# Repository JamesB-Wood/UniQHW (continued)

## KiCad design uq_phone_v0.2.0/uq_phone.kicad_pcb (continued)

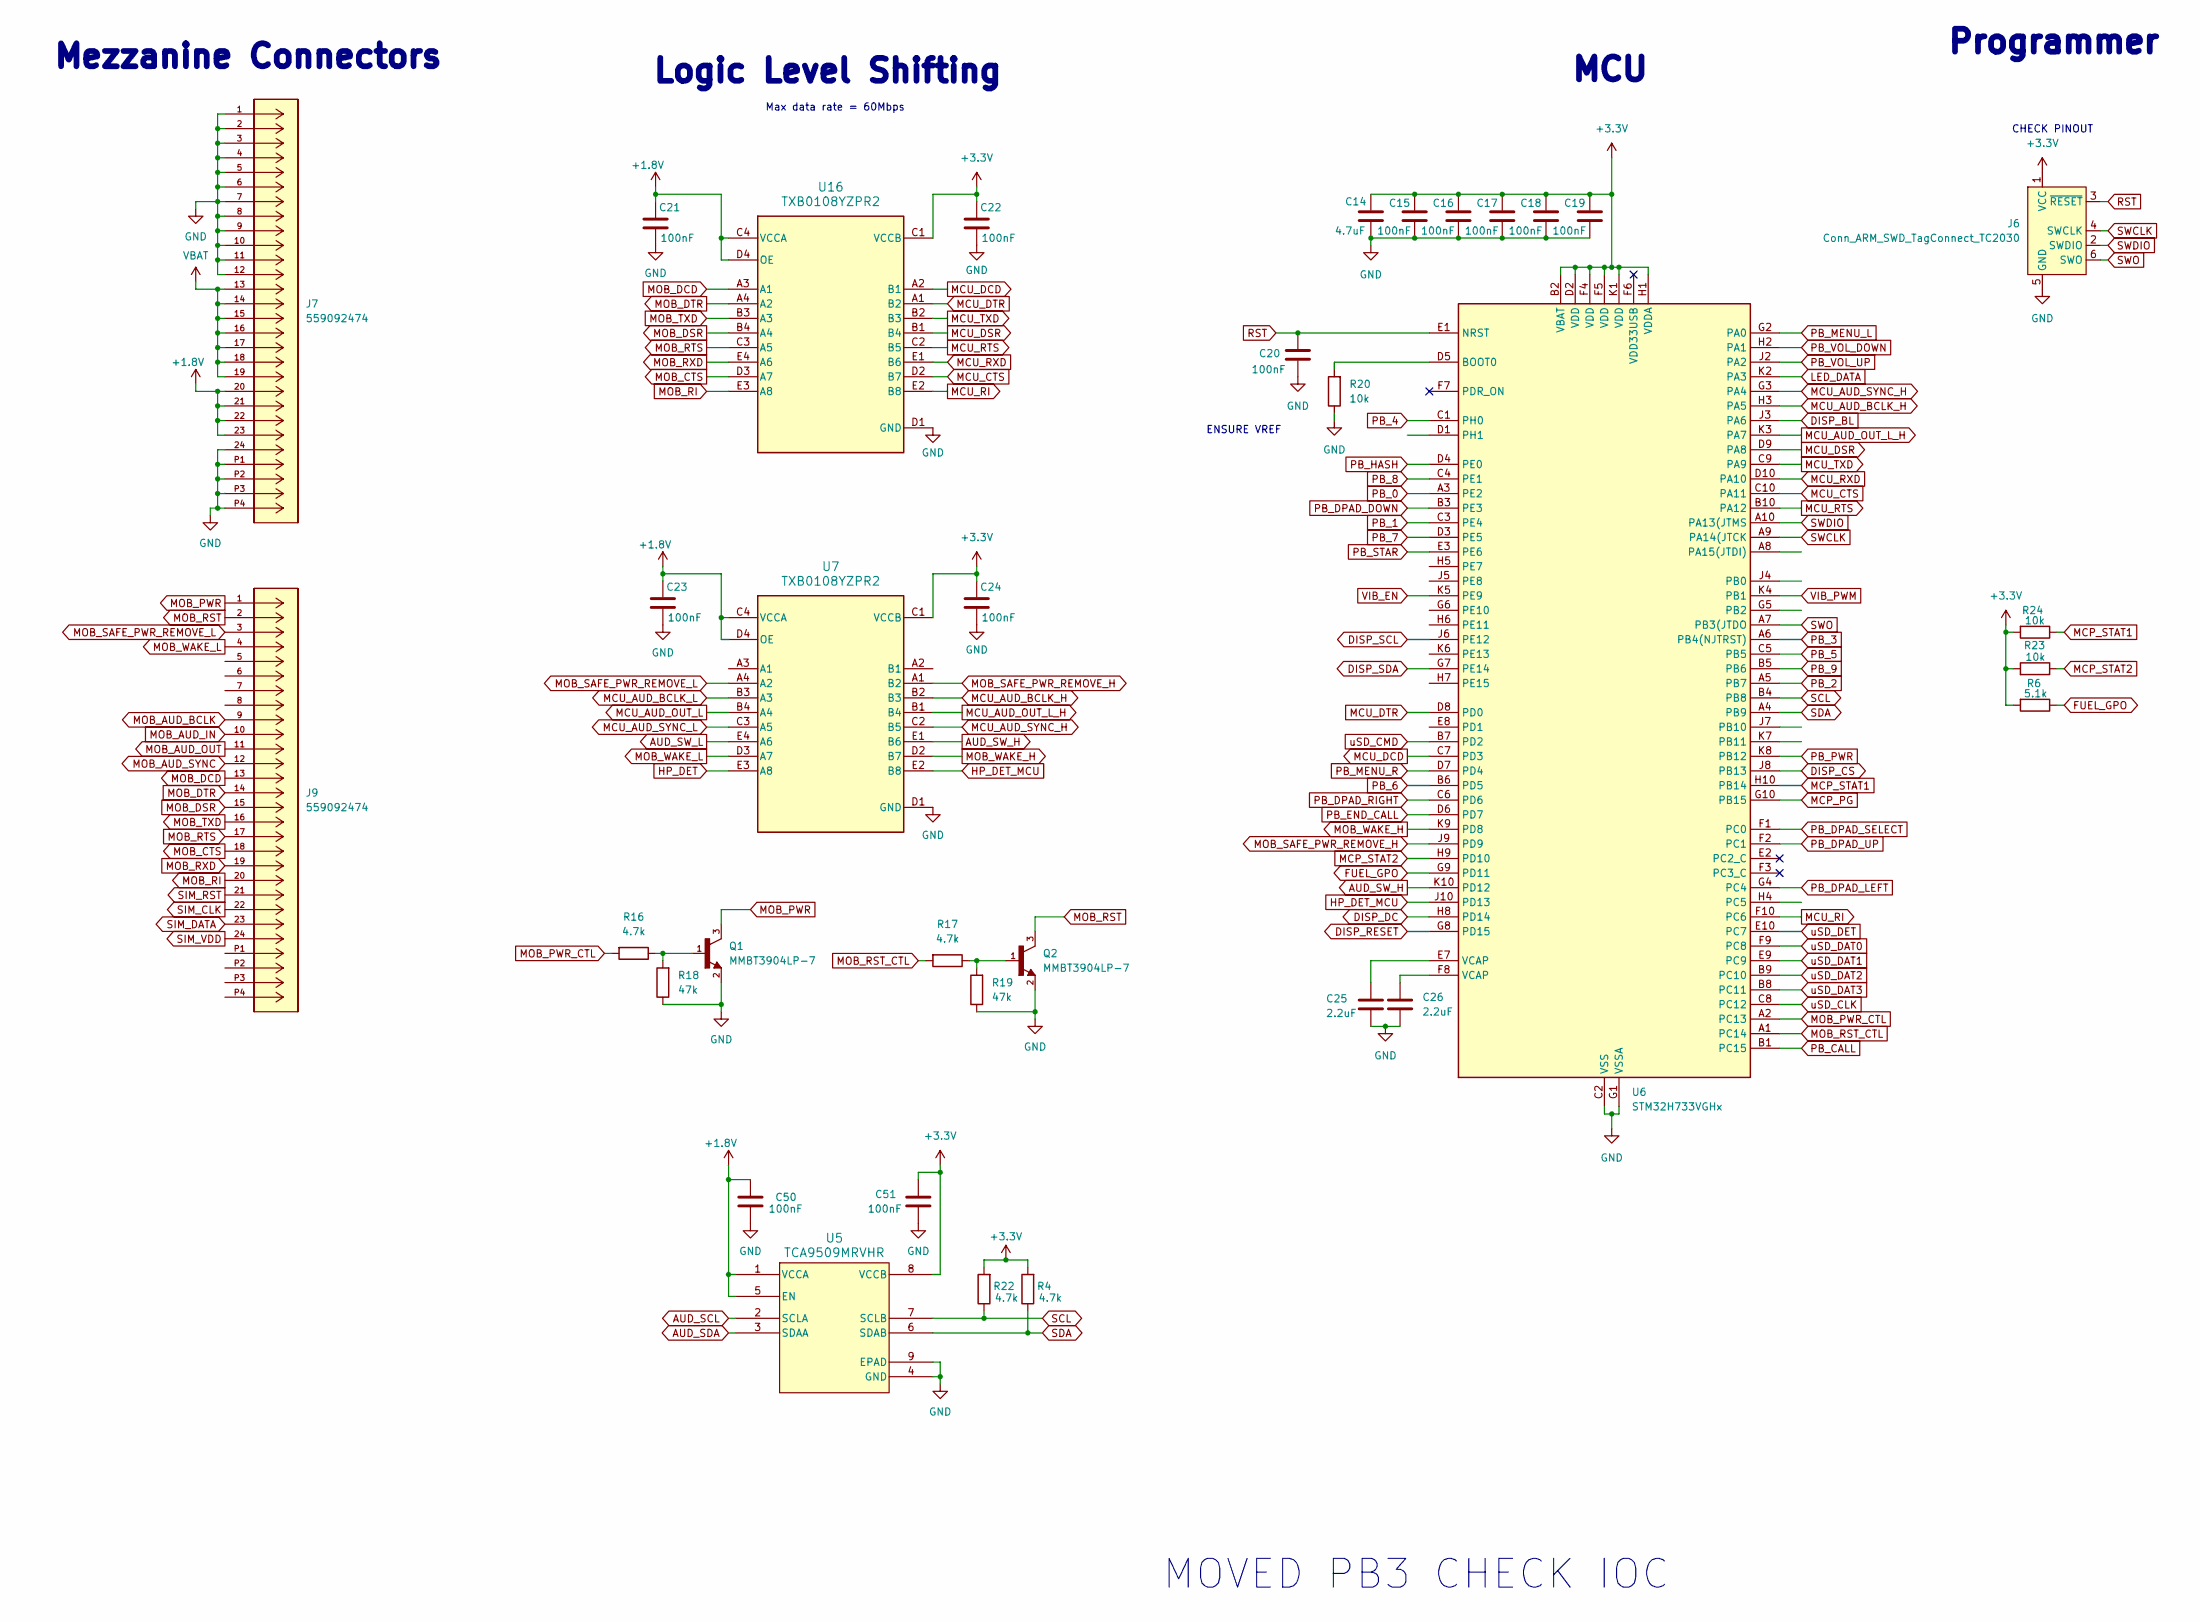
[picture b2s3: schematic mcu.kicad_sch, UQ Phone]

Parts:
C14: 4.7uF; C_0201_0603Metric; LCSC PN C335103
C15, C16, C17, C18, C19, C20, C21, C22, C23, C24, C50, C51: 100nF; C_0201_0603Metric; LCSC PN C160831
C25, C26: 2.2uF; C_0402_1005Metric; LCSC PN C107369
J6: Conn_ARM_SWD_TagConnect_TC2030; Tag-Connect_TC2030-IDC-FP_2x03_P1.27mm_Vertical
J7, J9: 559092474; CON_559092474; MANUFACTURER_PART_NUMBER 559092474; DigiKey_Part_Number WM3787TR-ND
Q1, Q2: MMBT3904LP-7; DFN101X61X53-3N; DigiKey_Part_Number MMBT3904LP-7DITR-ND
R4, R16, R17, R22: 4.7k; R_0201_0603Metric; LCSC PN C138135
R6: 5.1k; R_0201_0603Metric; LCSC PN C274341
R18, R19: 47k; R_0201_0603Metric; LCSC PN C138139
R20, R23, R24: 10k; R_0201_0603Metric; LCSC PN C106225
U5: TCA9509MRVHR; RVH8_0P4X0P4; LCSC PN C2652478
U6: STM32H733VGHx; TFBGA-100_8x8mm_Layout10x10_P0.8mm
U7, U16: TXB0108YZPR2; YZP20

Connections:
+1.8V: C21.1, C23.1, C50.1, J7.20, J7.21, J7.22, J7.23, U5.1 (VCCA), U5.5 (EN), U7.C4 (VCCA), U7.D4 (OE), U16.C4 (VCCA), U16.D4 (OE); also elsewhere on the board
+3.3V: C14.1, C15.2, C16.2, C17.2, C18.2, C19.2, C22.1, C24.1, C51.1, J6.1 (VCC), R4.2, R6.2, R22.2, R23.2, R24.2, U5.8 (VCCB), U6.B2 (VBAT), U6.D2 (VDD), U6.F4 (VDD), U6.F5 (VDD), U6.H1 (VDDA), U6.K1 (VDD), U7.C1 (VCCB), U16.C1 (VCCB); also elsewhere on the board
AUD_SCL: U5.2 (SCLA); also elsewhere on the board
AUD_SDA: U5.3 (SDAA); also elsewhere on the board
AUD_SW_H: U6.K10 (PD12), U7.E1 (B6)
AUD_SW_L: U7.E4 (A6); also elsewhere on the board
DISP_BL: U6.J3 (PA6); also elsewhere on the board
DISP_CS: U6.J8 (PB13); also elsewhere on the board
DISP_DC: U6.H8 (PD14); also elsewhere on the board
DISP_RESET: U6.G8 (PD15); also elsewhere on the board
DISP_SCL: U6.J6 (PE12); also elsewhere on the board
DISP_SDA: U6.G7 (PE14); also elsewhere on the board
FUEL_GPO: R6.1, U6.G9 (PD11); also elsewhere on the board
GND: C14.2, C15.1, C16.1, C17.1, C18.1, C19.1, C20.1, C21.2, C22.2, C23.2, C24.2, C25.2, C26.2, C50.2, C51.2, J6.5 (GND), J7.1, J7.2, J7.3, J7.4, J7.5, J7.6, J7.7, J7.8, J7.9, J7.10, J7.11, J7.12, J7.24, J7.P1, J7.P2, J7.P3, J7.P4, Q1.2, Q2.2, R18.1, R19.1, R20.1, U5.4 (GND), U5.9 (EPAD), U6.C2 (VSS), U6.E4 (VSS), U6.E5 (VSS), U6.E6 (VSS), U6.G1 (VSSA), U6.J1 (VSS), U7.D1 (GND), U16.D1 (GND); also elsewhere on the board
HP_DET: U7.E3 (A8); also elsewhere on the board
HP_DET_MCU: U6.J10 (PD13), U7.E2 (B8)
LED_DATA: U6.K2 (PA3); also elsewhere on the board
MCP_PG: U6.G10 (PB15); also elsewhere on the board
MCP_STAT1: R24.1, U6.H10 (PB14); also elsewhere on the board
MCP_STAT2: R23.1, U6.H9 (PD10); also elsewhere on the board
MCU_AUD_BCLK_H: U6.H3 (PA5), U7.B2 (B3)
MCU_AUD_BCLK_L: U7.B3 (A3); also elsewhere on the board
MCU_AUD_OUT_L: U7.B4 (A4); also elsewhere on the board
MCU_AUD_OUT_L_H: U6.K3 (PA7), U7.B1 (B4)
MCU_AUD_SYNC_H: U6.G3 (PA4), U7.C2 (B5)
MCU_AUD_SYNC_L: U7.C3 (A5); also elsewhere on the board
MCU_CTS: U6.C10 (PA11), U16.D2 (B7)
MCU_DCD: U6.C7 (PD3), U16.A2 (B1)
MCU_DSR: U6.D9 (PA8), U16.B1 (B4)
MCU_DTR: U6.D8 (PD0), U16.A1 (B2)
MCU_RI: U6.F10 (PC6), U16.E2 (B8)
MCU_RTS: U6.B10 (PA12), U16.C2 (B5)
MCU_RXD: U6.D10 (PA10), U16.E1 (B6)
MCU_TXD: U6.C9 (PA9), U16.B2 (B3)
MOB_AUD_BCLK: J9.9; also elsewhere on the board
MOB_AUD_IN: J9.10; also elsewhere on the board
MOB_AUD_OUT: J9.11; also elsewhere on the board
MOB_AUD_SYNC: J9.12; also elsewhere on the board
MOB_CTS: J9.18, U16.D3 (A7); also elsewhere on the board
MOB_DCD: J9.13, U16.A3 (A1); also elsewhere on the board
MOB_DSR: J9.15, U16.B4 (A4); also elsewhere on the board
MOB_DTR: J9.14, U16.A4 (A2); also elsewhere on the board
MOB_PWR: J9.1, Q1.3; also elsewhere on the board
MOB_PWR_CTL: R16.2, U6.A2 (PC13)
MOB_RI: J9.20, U16.E3 (A8); also elsewhere on the board
MOB_RST: J9.2, Q2.3; also elsewhere on the board
MOB_RST_CTL: R17.2, U6.A1 (PC14)
MOB_RTS: J9.17, U16.C3 (A5); also elsewhere on the board
MOB_RXD: J9.19, U16.E4 (A6); also elsewhere on the board
MOB_SAFE_PWR_REMOVE_H: U6.J9 (PD9), U7.A1 (B2)
MOB_SAFE_PWR_REMOVE_L: J9.3, U7.A4 (A2); also elsewhere on the board
MOB_TXD: J9.16, U16.B3 (A3); also elsewhere on the board
MOB_WAKE_H: U6.K9 (PD8), U7.D2 (B7)
MOB_WAKE_L: J9.4, U7.D3 (A7); also elsewhere on the board
unnamed: C25.1, U6.E7 (VCAP)
unnamed: C26.1, U6.F8 (VCAP)
unnamed: Q1.1, R16.1, R18.2
unnamed: Q2.1, R17.1, R19.2
unnamed: R20.2, U6.D5 (BOOT0)
PB_0: U6.A3 (PE2); also elsewhere on the board
PB_1: U6.C3 (PE4); also elsewhere on the board
PB_2: U6.A5 (PB7); also elsewhere on the board
PB_3: U6.A6 (PB4(NJTRST)); also elsewhere on the board
PB_4: U6.C1 (PH0); also elsewhere on the board
PB_5: U6.C5 (PB5); also elsewhere on the board
PB_6: U6.B6 (PD5); also elsewhere on the board
PB_7: U6.D3 (PE5); also elsewhere on the board
PB_8: U6.C4 (PE1); also elsewhere on the board
PB_9: U6.B5 (PB6); also elsewhere on the board
PB_CALL: U6.B1 (PC15); also elsewhere on the board
PB_DPAD_DOWN: U6.B3 (PE3); also elsewhere on the board
PB_DPAD_LEFT: U6.G4 (PC4); also elsewhere on the board
PB_DPAD_RIGHT: U6.C6 (PD6); also elsewhere on the board
PB_DPAD_SELECT: U6.F1 (PC0); also elsewhere on the board
PB_DPAD_UP: U6.F2 (PC1); also elsewhere on the board
PB_END_CALL: U6.D6 (PD7); also elsewhere on the board
PB_HASH: U6.D4 (PE0); also elsewhere on the board
PB_MENU_L: U6.G2 (PA0); also elsewhere on the board
PB_MENU_R: U6.D7 (PD4); also elsewhere on the board
PB_PWR: U6.K8 (PB12); also elsewhere on the board
PB_STAR: U6.E3 (PE6); also elsewhere on the board
PB_VOL_DOWN: U6.H2 (PA1); also elsewhere on the board
PB_VOL_UP: U6.J2 (PA2); also elsewhere on the board
RST: C20.2, J6.3 (~RESET), U6.E1 (NRST)
SCL: R22.1, U5.7 (SCLB), U6.B4 (PB8); also elsewhere on the board
SDA: R4.1, U5.6 (SDAB), U6.A4 (PB9); also elsewhere on the board
SIM_CLK: J9.22; also elsewhere on the board
SIM_DATA: J9.23; also elsewhere on the board
SIM_RST: J9.21; also elsewhere on the board
SIM_VDD: J9.24; also elsewhere on the board
SWCLK: J6.4 (SWCLK), U6.A9 (PA14(JTCK)
SWDIO: J6.2 (SWDIO), U6.A10 (PA13(JTMS)
SWO: J6.6 (SWO), U6.A7 (PB3(JTDO)
VBAT: J7.13, J7.14, J7.15, J7.16, J7.17, J7.18, J7.19; also elsewhere on the board
VIB_EN: U6.K5 (PE9); also elsewhere on the board
VIB_PWM: U6.K4 (PB1); also elsewhere on the board
uSD_CLK: U6.C8 (PC12); also elsewhere on the board
uSD_CMD: U6.B7 (PD2); also elsewhere on the board
uSD_DAT0: U6.F9 (PC8); also elsewhere on the board
uSD_DAT1: U6.E9 (PC9); also elsewhere on the board
uSD_DAT2: U6.B9 (PC10); also elsewhere on the board
uSD_DAT3: U6.B8 (PC11); also elsewhere on the board
uSD_DET: U6.E10 (PC7); also elsewhere on the board

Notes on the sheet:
Max data rate = 60Mbps
MOVED PB3 CHECK IOC
Programmer
MCU
Mezzanine Connectors
CHECK PINOUT
Logic Level Shifting
ENSURE VREF

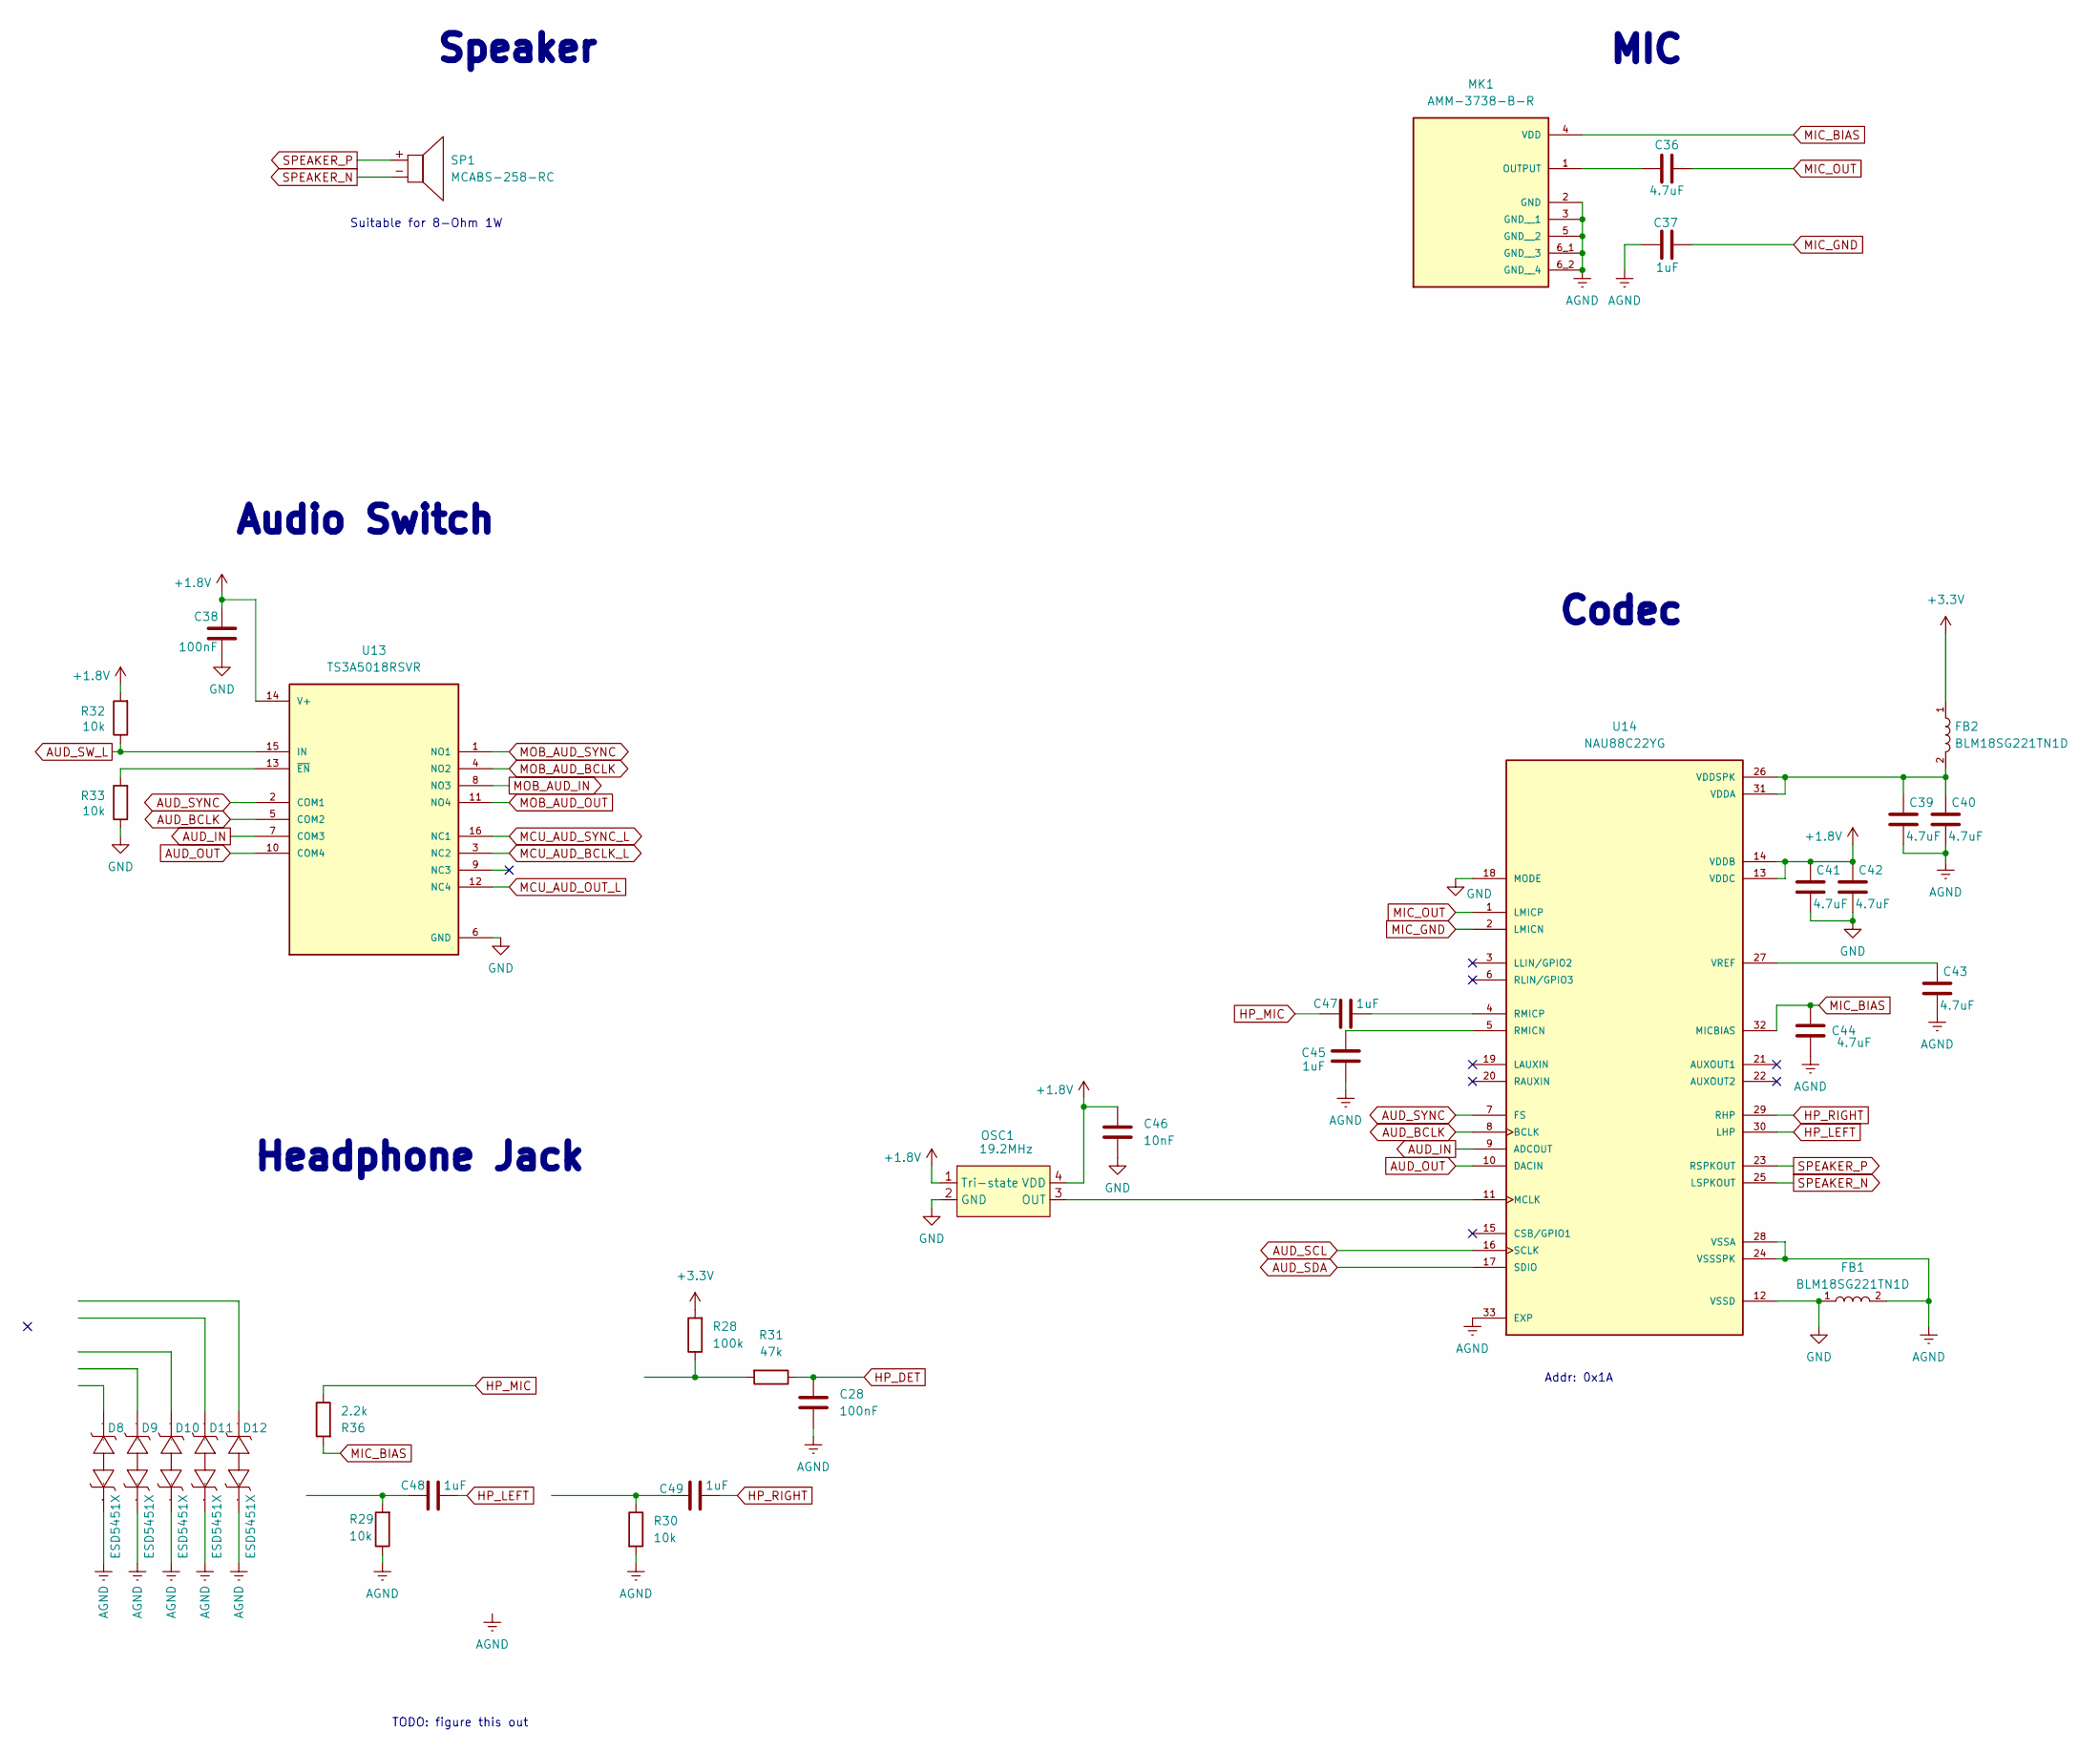
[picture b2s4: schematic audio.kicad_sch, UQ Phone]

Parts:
C28, C38: 100nF; C_0201_0603Metric; LCSC PN C160831
C36, C39, C40, C41, C42, C43, C44: 4.7uF; C_0201_0603Metric; LCSC PN C335103
C37, C45, C47, C48, C49: 1uF; C_0201_0603Metric; LCSC PN C53067
C46: 10nF; C_0402_1005Metric; LCSC PN C15195
D8, D9, D10, D11, D12: ESD5451X; WBFBP-02C_L1.0-W0.6-BI; Manufacturer Part ESD5451X-2/TR; LCSC Part Name ESD5451X-2/TR
FB1, FB2: BLM18SG221TN1D; BEADC1608X65N; DigiKey_Part_Number 490-5225-2-ND
MK1: AMM-3738-B-R; MIC_AMM-3738-B-R; PARTREV A; DigiKey_Part_Number 668-AMM-3738-B-RTR-ND
OSC1: 19.2MHz; OSC-SMD_4P-L2.0-W1.6-BL; Manufacturer Part OT7EL89CJI-111YLC-19.2M; LCSC Part Name YSO110TR 19.2MHZ 4P 2016 1.8V-3.3V ±10P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
R28: 100k; R_0201_0603Metric; LCSC PN C106224
R29, R30, R32, R33: 10k; R_0201_0603Metric; LCSC PN C106225
R31: 47k; R_0201_0603Metric; LCSC PN C138139
R36: 2.2k; R_0201_0603Metric; LCSC PN C142018
SP1: MCABS-258-RC
U13: TS3A5018RSVR; QFN40P260X180X55-16N; PARTREV 4220314/C 02/2020; DigiKey_Part_Number 296-27552-2-ND
U14: NAU88C22YG; QFN50P500X500X80-33N; PARTREV 3.3; DigiKey_Part_Number NAU88C22YG-ND

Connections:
+1.8V: C38.1, C41.1, C42.1, C46.1, OSC1.1 (Tri-state), OSC1.4 (VDD), R32.2, U13.14 (V+), U14.13 (VDDC), U14.14 (VDDB); also elsewhere on the board
+3.3V: FB2.1, R28.2; also elsewhere on the board
AGND: C28.2, C37.1, C39.2, C40.2, C43.2, C44.2, C45.2, D8.1, D9.1, D10.1, D11.1, D12.1, FB1.2, MK1.2 (GND), MK1.3 (GND__1), MK1.5 (GND__2), MK1.6_1 (GND__3), MK1.6_2 (GND__4), R29.1, R30.2, U14.24 (VSSSPK), U14.28 (VSSA), U14.33 (EXP); also elsewhere on the board
AUD_BCLK: U13.5 (COM2), U14.8 (BCLK)
AUD_IN: U13.7 (COM3), U14.9 (ADCOUT)
AUD_OUT: U13.10 (COM4), U14.10 (DACIN)
AUD_SCL: U14.16 (SCLK); also elsewhere on the board
AUD_SDA: U14.17 (SDIO); also elsewhere on the board
AUD_SW_L: R32.1, U13.15 (IN); also elsewhere on the board
AUD_SYNC: U13.2 (COM1), U14.7 (FS)
GND: C38.2, C41.2, C42.2, C46.2, FB1.1, OSC1.2 (GND), R33.1, U13.6 (GND), U14.12 (VSSD), U14.18 (MODE); also elsewhere on the board
HP_DET: C28.1, R31.1; also elsewhere on the board
HP_LEFT: C48.1, U14.30 (LHP)
HP_MIC: C47.2, R36.1
HP_RIGHT: C49.1, U14.29 (RHP)
MCU_AUD_BCLK_L: U13.3 (NC2); also elsewhere on the board
MCU_AUD_OUT_L: U13.12 (NC4); also elsewhere on the board
MCU_AUD_SYNC_L: U13.16 (NC1); also elsewhere on the board
MIC_BIAS: C44.1, MK1.4 (VDD), R36.2, U14.32 (MICBIAS)
MIC_GND: C37.2, U14.2 (LMICN)
MIC_OUT: C36.2, U14.1 (LMICP)
MOB_AUD_BCLK: U13.4 (NO2); also elsewhere on the board
MOB_AUD_IN: U13.8 (NO3); also elsewhere on the board
MOB_AUD_OUT: U13.11 (NO4); also elsewhere on the board
MOB_AUD_SYNC: U13.1 (NO1); also elsewhere on the board
unnamed: C48.2, R29.2
unnamed: C49.2, R30.1
unnamed: C36.1, MK1.1 (OUTPUT)
unnamed: OSC1.3 (OUT), U14.11 (MCLK)
unnamed: R28.1, R31.2
unnamed: R33.2, U13.13 (~EN)
unnamed: C45.1, U14.5 (RMICN)
unnamed: C47.1, U14.4 (RMICP)
unnamed: C39.1, C40.1, FB2.2, U14.26 (VDDSPK), U14.31 (VDDA)
unnamed: C43.1, U14.27 (VREF)
SPEAKER_N: SP1.-, U14.25 (LSPKOUT)
SPEAKER_P: SP1.+, U14.23 (RSPKOUT)

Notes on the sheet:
Suitable for 8-Ohm 1W
Addr: 0x1A
TODO: figure this out
Codec
Headphone Jack
Speaker
MIC
Audio Switch

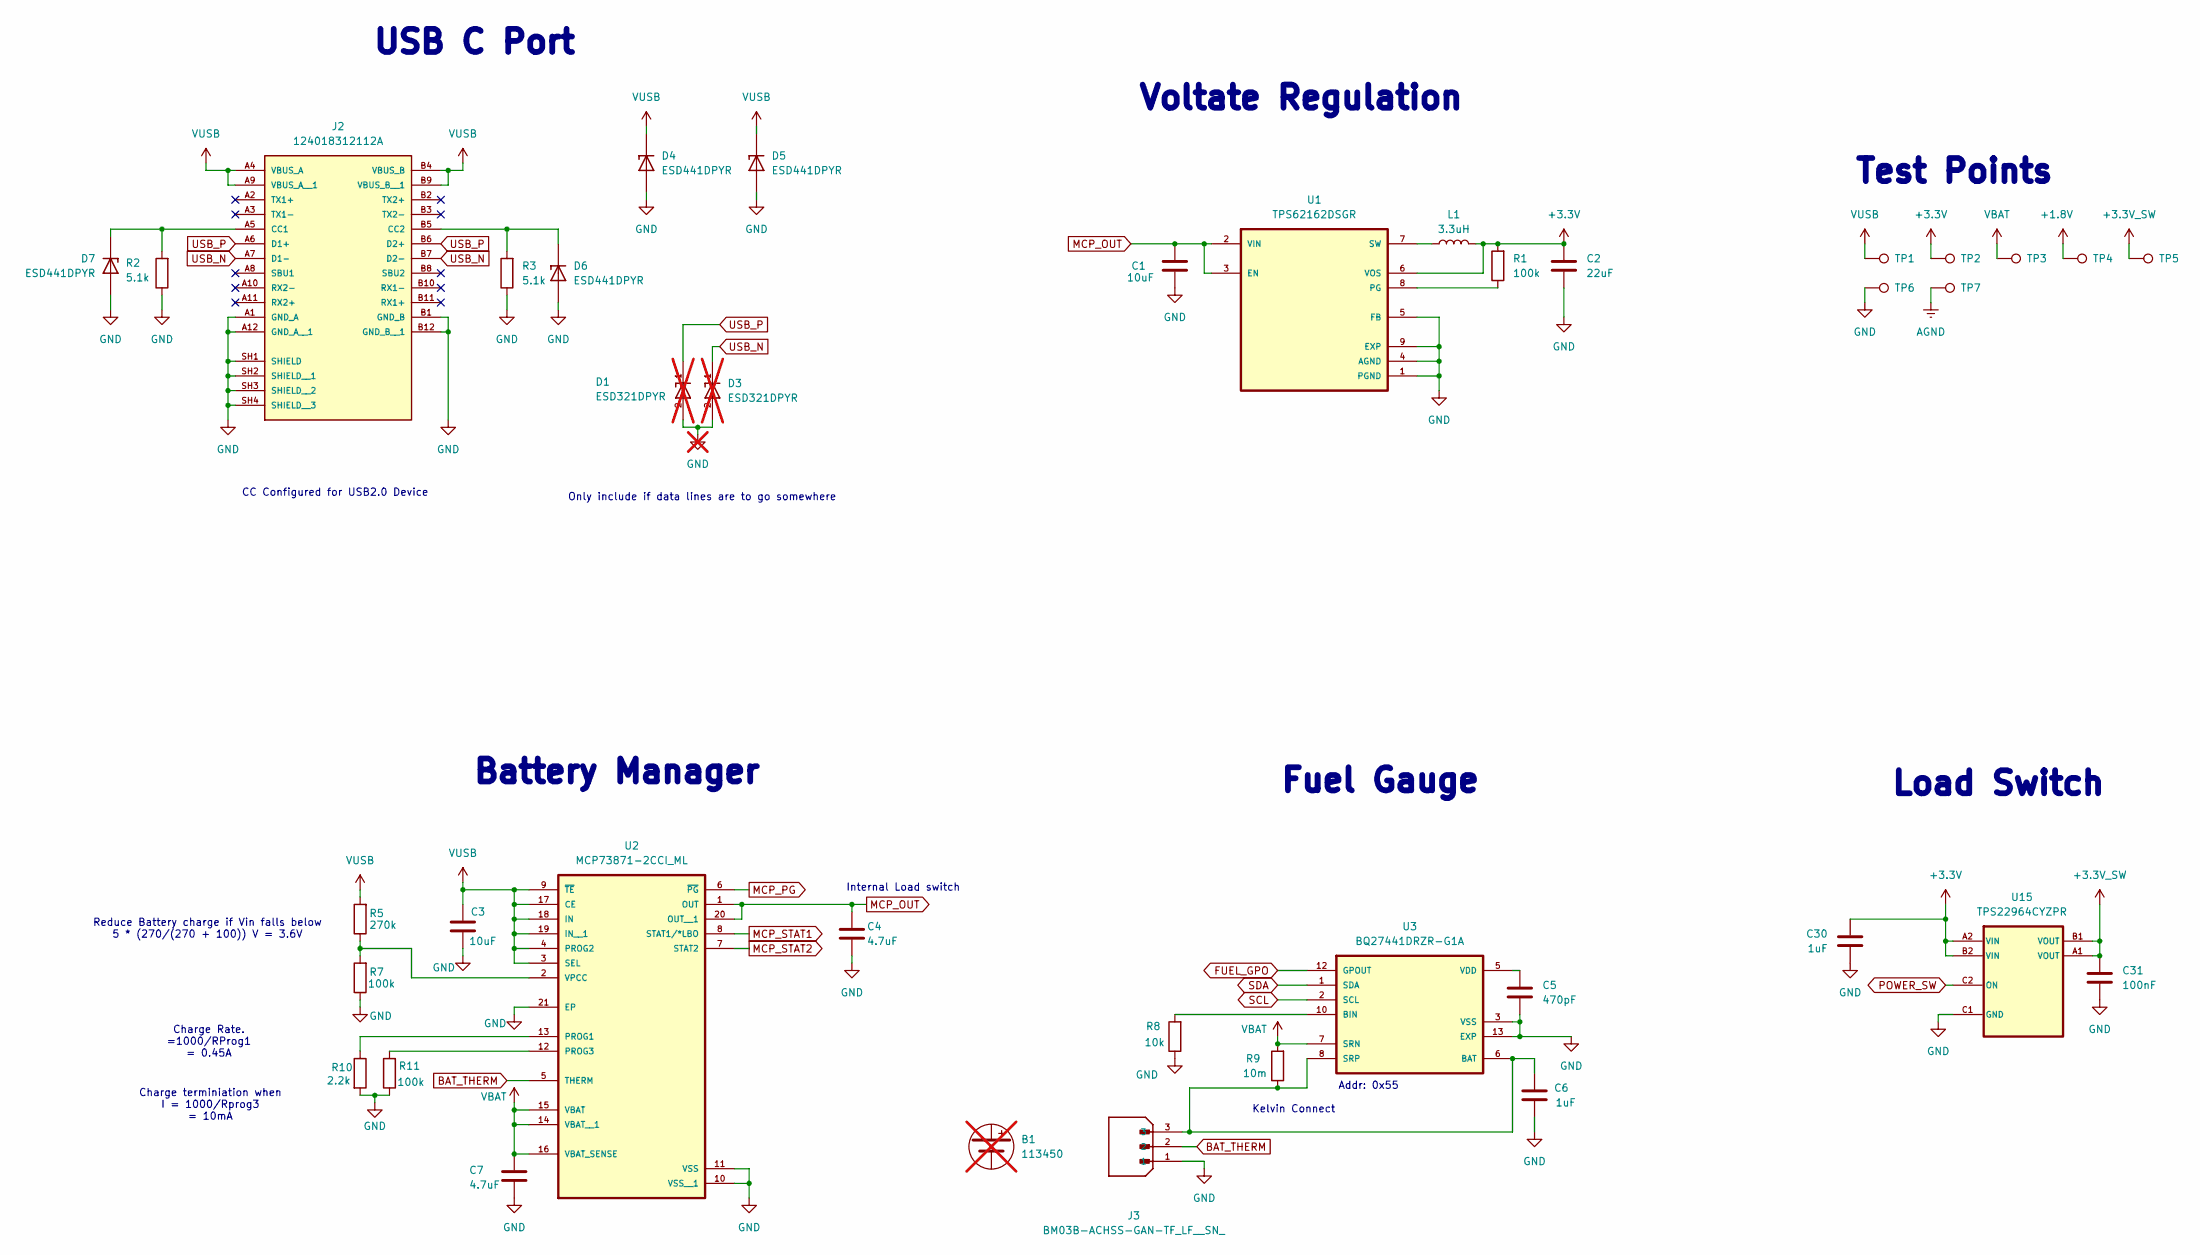
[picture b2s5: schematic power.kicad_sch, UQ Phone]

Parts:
B1: 113450; not fitted
C1, C3: 10uF; C_0603_1608Metric; LCSC PN C2168196
C2: 22uF; C_0603_1608Metric; LCSC PN C3020456
C4, C7: 4.7uF; C_0201_0603Metric; LCSC PN C335103
C5: 470pF; C_0402_1005Metric; LCSC PN C26412
C6, C30: 1uF; C_0201_0603Metric; LCSC PN C53067
C31: 100nF; C_0201_0603Metric; LCSC PN C160831
D1, D3: ESD321DPYR; TVS_ESD321DPYR; PARTREV B; DigiKey_Part_Number 296-51108-2-ND; not fitted
D4, D5, D6, D7: ESD441DPYR; DIODFN60X30X32-2N; PARTREV B; LCSC PN C22427765
J2: 124018312112A; AMPHENOL_124018312112A; PARTREV 1; DigiKey_Part_Number 124018312112ATR-ND
J3: BM03B-ACHSS-GAN-TF_LF__SN_; JST_BM03B-ACHSS-GAN-TF_LF__SN_; PARTREV N/A
L1: 3.3uH; INDC2520X120N; DigiKey_Part_Number 587-3227-2-ND
R1, R7, R11: 100k; R_0201_0603Metric; LCSC PN C106224
R2, R3: 5.1k; R_0201_0603Metric; LCSC PN C274341
R5: 270k; R_0201_0603Metric; LCSC PN C851694
R8: 10k; R_0201_0603Metric; LCSC PN C106225
R9: 10m; R_0805_2012Metric; LCSC PN C723359
R10: 2.2k; R_0201_0603Metric; LCSC PN C142018
TP1, TP2, TP3, TP4, TP5, TP6, TP7: TestPoint; TestPoint_Pad_D1.5mm
U1: TPS62162DSGR; SON50P200X200X80-9N; PARTREV E; DigiKey_Part_Number 296-43671-2-ND
U2: MCP73871-2CCI_ML; QFN50P400X400X100-21N; LCSC PN C5121473
U3: BQ27441DRZR-G1A; IC_BQ27441DRZR-G1A; LCSC PN C473397
U15: TPS22964CYZPR; IC_SN74LVC2G34YZPR; LCSC PN C431579

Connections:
+1.8V: TP4.1; also elsewhere on the board
+3.3V: C2.1, C30.1, L1.2, R1.2, TP2.1, U1.6 (VOS), U15.A2 (VIN), U15.B2 (VIN); also elsewhere on the board
+3.3V_SW: C31.1, TP5.1, U15.A1 (VOUT), U15.B1 (VOUT); also elsewhere on the board
AGND: TP7.1; also elsewhere on the board
BAT_THERM: J3.2, U2.5 (THERM)
FUEL_GPO: U3.12 (GPOUT); also elsewhere on the board
GND: C1.1, C2.2, C3.2, C4.2, C5.2, C6.2, C7.2, C30.2, C31.2, D1.2, D3.2, D4.2, D5.2, D6.2, D7.2, J2.A1 (GND_A), J2.A12 (GND_A__1), J2.B1 (GND_B), J2.B12 (GND_B__1), J2.SH1 (SHIELD), J2.SH2 (SHIELD__1), J2.SH3 (SHIELD__2), J2.SH4 (SHIELD__3), J3.1, R2.1, R3.1, R7.1, R8.1, R10.2, R11.1, TP6.1, U1.1 (PGND), U1.4 (AGND), U1.5 (FB), U1.9 (EXP), U2.10 (VSS__1), U2.11 (VSS), U2.21 (EP), U3.3 (VSS), U3.13 (EXP), U15.C1 (GND); also elsewhere on the board
MCP_OUT: C1.2, C4.1, U1.2 (VIN), U1.3 (EN), U2.1 (OUT), U2.20 (OUT__1)
MCP_PG: U2.6 (~PG); also elsewhere on the board
MCP_STAT1: U2.8 (STAT1/*LBO); also elsewhere on the board
MCP_STAT2: U2.7 (STAT2); also elsewhere on the board
unnamed: D7.1, J2.A5 (CC1), R2.2
unnamed: D6.1, J2.B5 (CC2), R3.2
unnamed: R1.1, U1.8 (PG)
unnamed: L1.1, U1.7 (SW)
unnamed: R10.1, U2.13 (PROG1)
unnamed: R11.2, U2.12 (PROG3)
unnamed: R5.1, R7.2, U2.2 (VPCC)
unnamed: C6.1, J3.3, R9.1, U3.6 (BAT), U3.8 (SRP)
unnamed: R8.2, U3.10 (BIN)
unnamed: C5.1, U3.5 (VDD)
POWER_SW: U15.C2 (ON)
SCL: U3.2 (SCL); also elsewhere on the board
SDA: U3.1 (SDA); also elsewhere on the board
USB_N: D3.1, J2.A7 (D1-), J2.B7 (D2-)
USB_P: D1.1, J2.A6 (D1+), J2.B6 (D2+)
VBAT: C7.1, R9.2, TP3.1, U2.14 (VBAT__1), U2.15 (VBAT), U2.16 (VBAT_SENSE), U3.7 (SRN); also elsewhere on the board
VUSB: C3.1, D4.1, D5.1, J2.A4 (VBUS_A), J2.A9 (VBUS_A__1), J2.B4 (VBUS_B), J2.B9 (VBUS_B__1), R5.2, TP1.1, U2.3 (SEL), U2.4 (PROG2), U2.9 (~TE), U2.17 (CE), U2.18 (IN), U2.19 (IN__1)

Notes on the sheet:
Battery Manager
CC Configured for USB2.0 Device
Charge Rate. =1000/RProg1 = 0.45A
Load Switch
Addr: 0x55
Voltate Regulation
Kelvin Connect
Reduce Battery charge if Vin falls below 5 * (270/(270 + 100)) V = 3.6V
Internal Load switch
Only include if data lines are to go somewhere
Charge terminiation when I = 1000/Rprog3 = 10mA
Fuel Gauge
USB C Port
Test Points
